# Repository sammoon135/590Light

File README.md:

# 590Light
Create a lightweight, multi-function light for the *individual* design challenge

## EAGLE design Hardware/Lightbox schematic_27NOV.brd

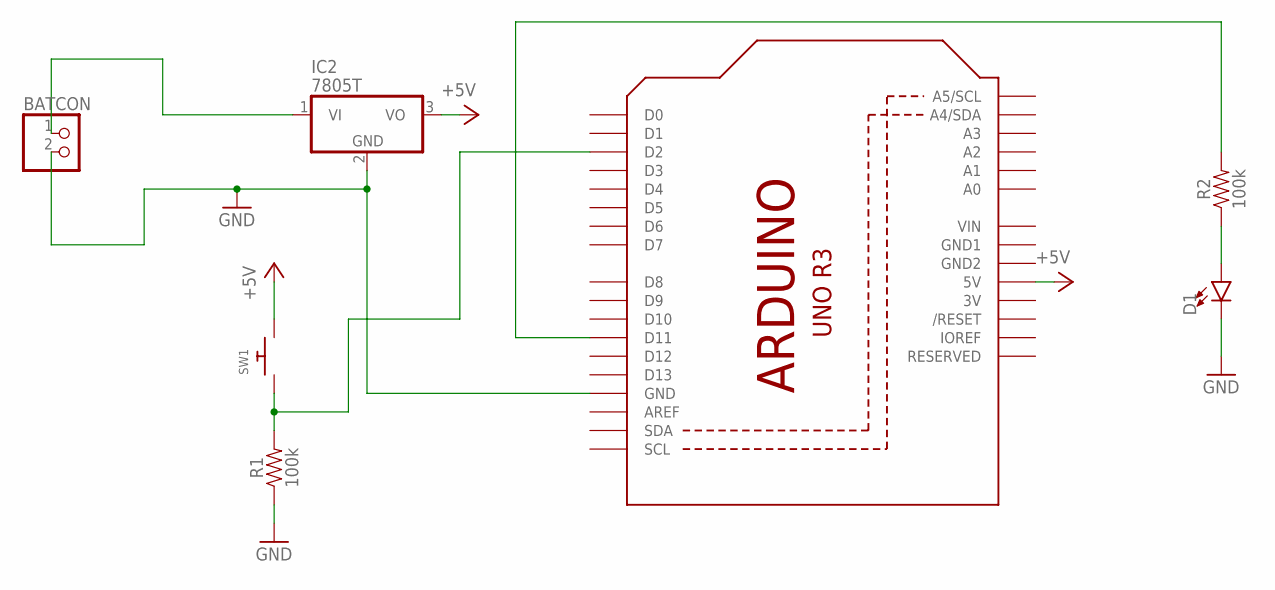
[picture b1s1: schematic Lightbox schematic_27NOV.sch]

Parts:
BATCON: PINHD-1X2; 1X02
D1: LED3MM; LED_3MM
IC2: 7805T; TO220H
R1, R2: 100k; AXIAL-0.3
SW1: SWITCH_PUSHBUTTONSOFTTOUCHSMD_SJ; PUSHBUTTON_SMD_SJ
U1: ARDUINOR3-DIMENSION; ARDUINOR3

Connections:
3V: U1.3V
+5V: IC2.3 (VO), SW1.P$2, U1.5V
GND: BATCON.2, D1.K (C), IC2.2 (GND), R1.P$1 (1), U1.GND
GND1: U1.GND1
GND2: U1.GND2
unnamed: BATCON.1, IC2.1 (VI)
unnamed: R1.P$2 (2), SW1.P$1, U1.D2
unnamed: R2.P$2 (2), U1.D11
unnamed: D1.A, R2.P$1 (1)
VIN: U1.VIN

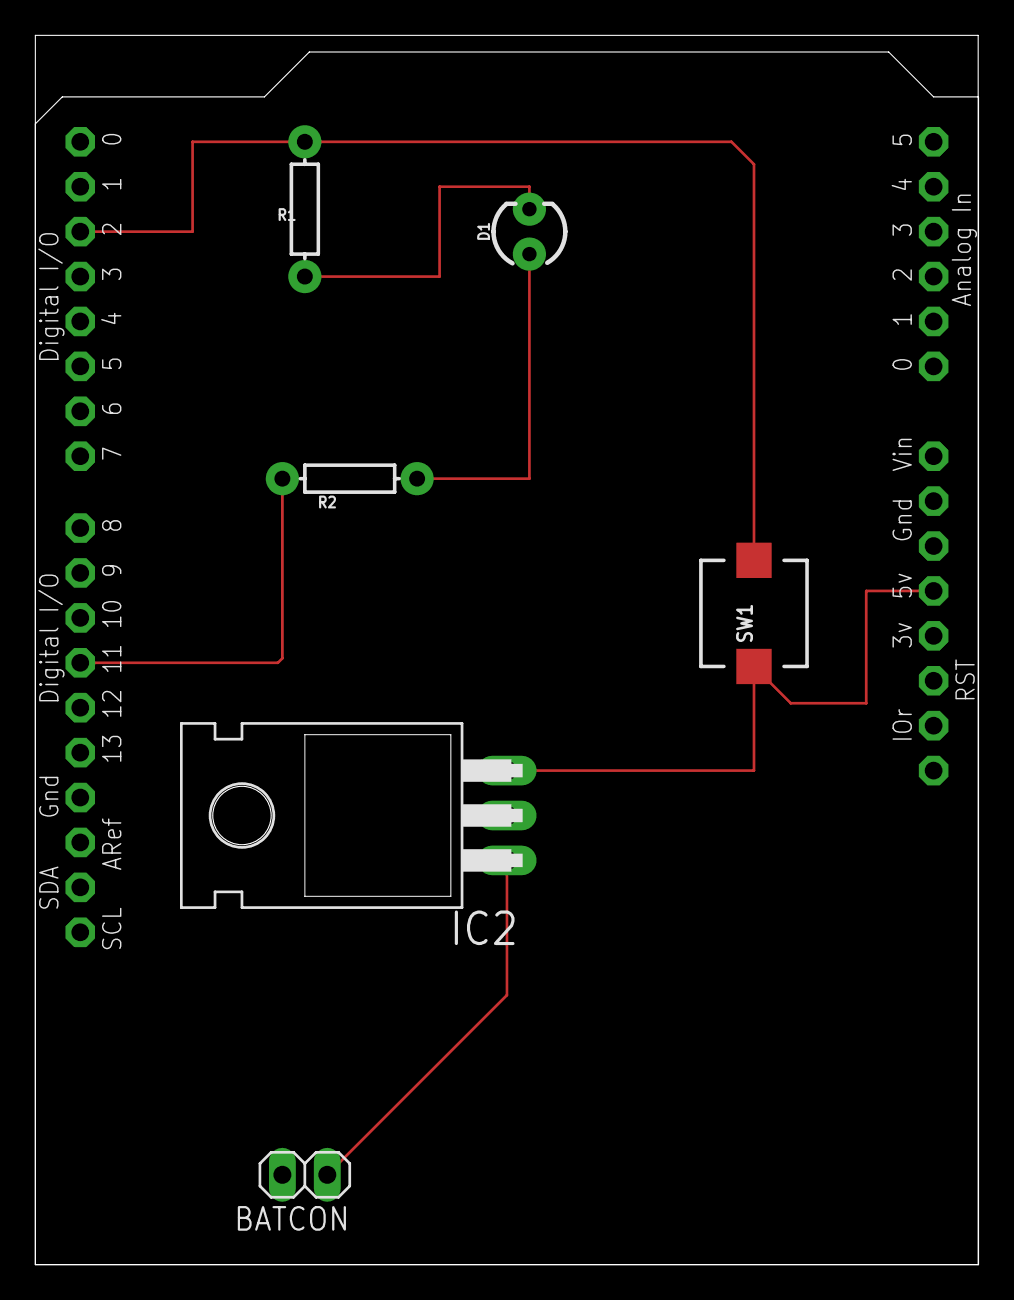
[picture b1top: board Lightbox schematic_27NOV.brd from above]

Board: 2 copper layers, 53.3 x 69.5 mm, 7 parts (0 on the bottom side), 6 nets.

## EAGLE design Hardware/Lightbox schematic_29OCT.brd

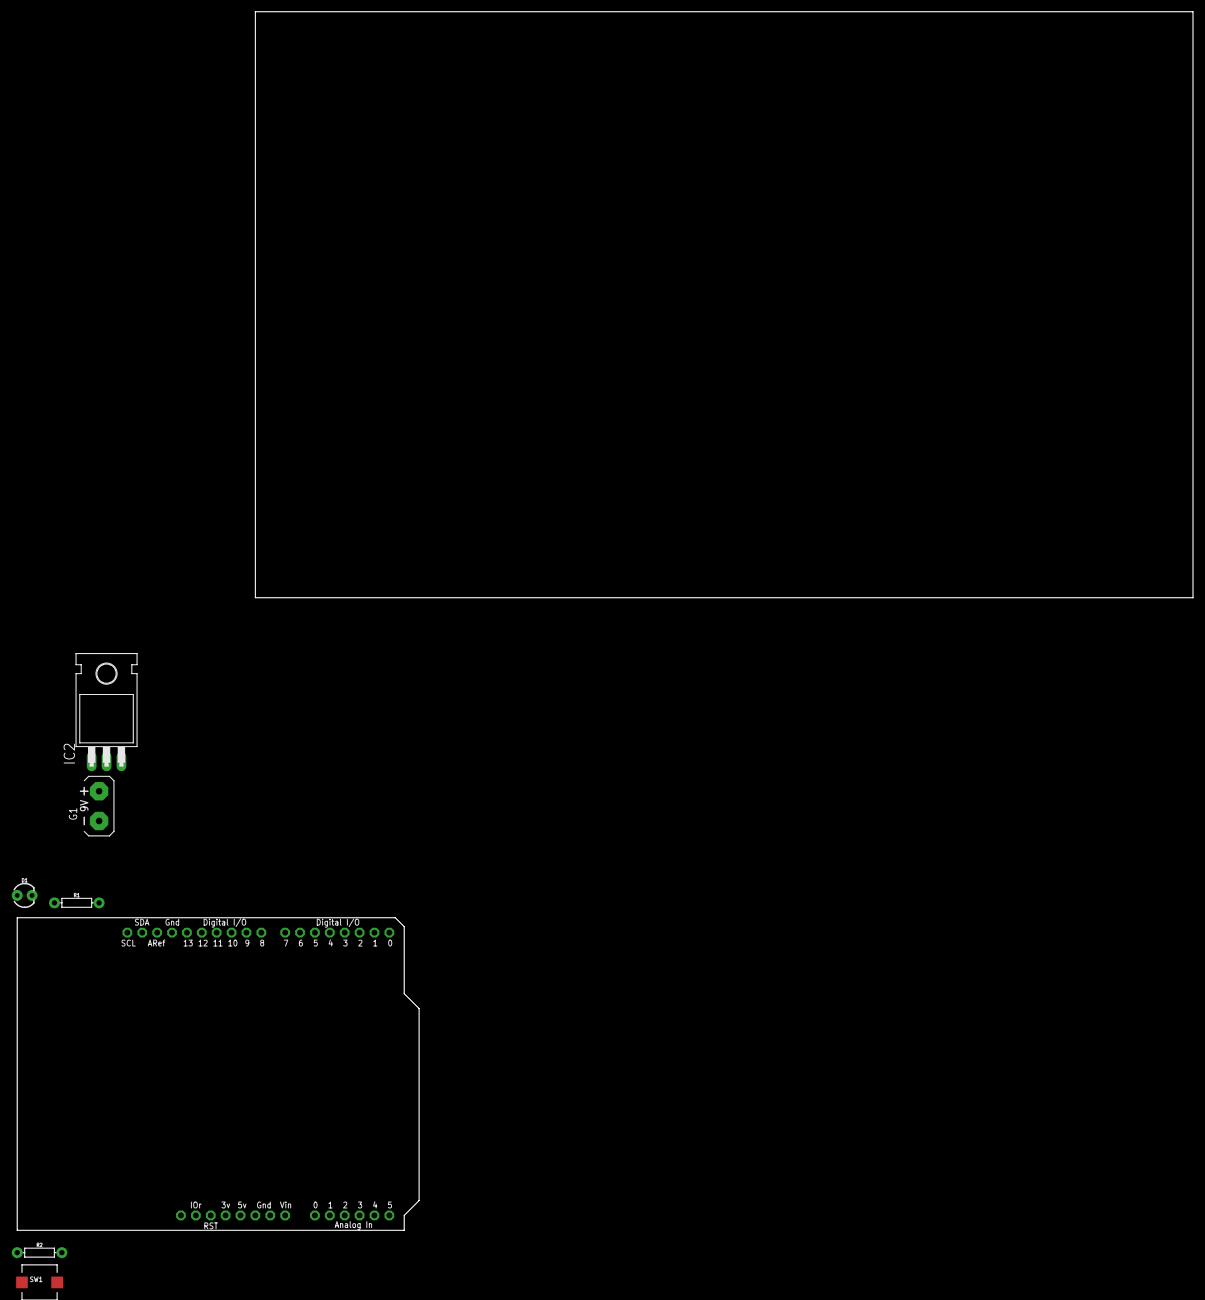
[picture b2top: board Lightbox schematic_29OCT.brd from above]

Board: 2 copper layers, 7 parts (0 on the bottom side), 6 nets, no tracks yet.

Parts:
D1: LED_3MM
G1: AB9V
IC2: 7805T; TO220H
R1, R2: 100k; AXIAL-0.3
SW1: PUSHBUTTON_SMD_SJ
U1: ARDUINOR3-DIMENSION; ARDUINOR3

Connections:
5V: IC2.3, SW1.P$2
GND: D1.K, G1.-, IC2.2, R1.P$1, U1.GND
unnamed: G1.+, IC2.1
unnamed: R1.P$2, SW1.P$1, U1.D0
unnamed: R2.P$2, U1.D11
unnamed: D1.A, R2.P$1

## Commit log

2018-11-01 Add files via upload
    Hand-drawn schematic ROUGH
2018-11-01 Add files via upload
    Circuit schematics in EAGLE
2018-11-08 Milestone 4
    Circuit schematic, board, and code for milestone 4.
2018-11-08 Circuit and Board PNG (Milestone 4)
    Here is a screenshot of my circuit schematic and board (I couldn't figure out how to PDF).
2018-11-08 v0.2.0
    Milestone 4 Deliverables: updated board, schematic, circuit
2018-11-19 v0.3.0
    Milestone 5 - CAD Drawing and 3D rendering for lightbox
2018-11-27 New CAD - 26 NOV
    Updated CAD files finalized 26 NOV
2018-11-28 v0.2.1
    Updates to EDA files (w/screenshots)
2018-12-14 Final
    Final uploads for lightbox project

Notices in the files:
parts and their libraries:
SparkFun-Resistors: Licensing: Creative Commons ShareAlike 4.0 International - https://creativecommons.org/licenses/by-sa/4.0
